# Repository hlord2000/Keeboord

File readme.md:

# Keeboord
## Created for the [Mechanical Keyboard Club at Georgia Tech](https://www.instagram.com/gt.keyboards)

This is a mechanical keyboard for Cherry switches.  It utilizes no diodes, instead registering button presses by using I2C I/O expanders.

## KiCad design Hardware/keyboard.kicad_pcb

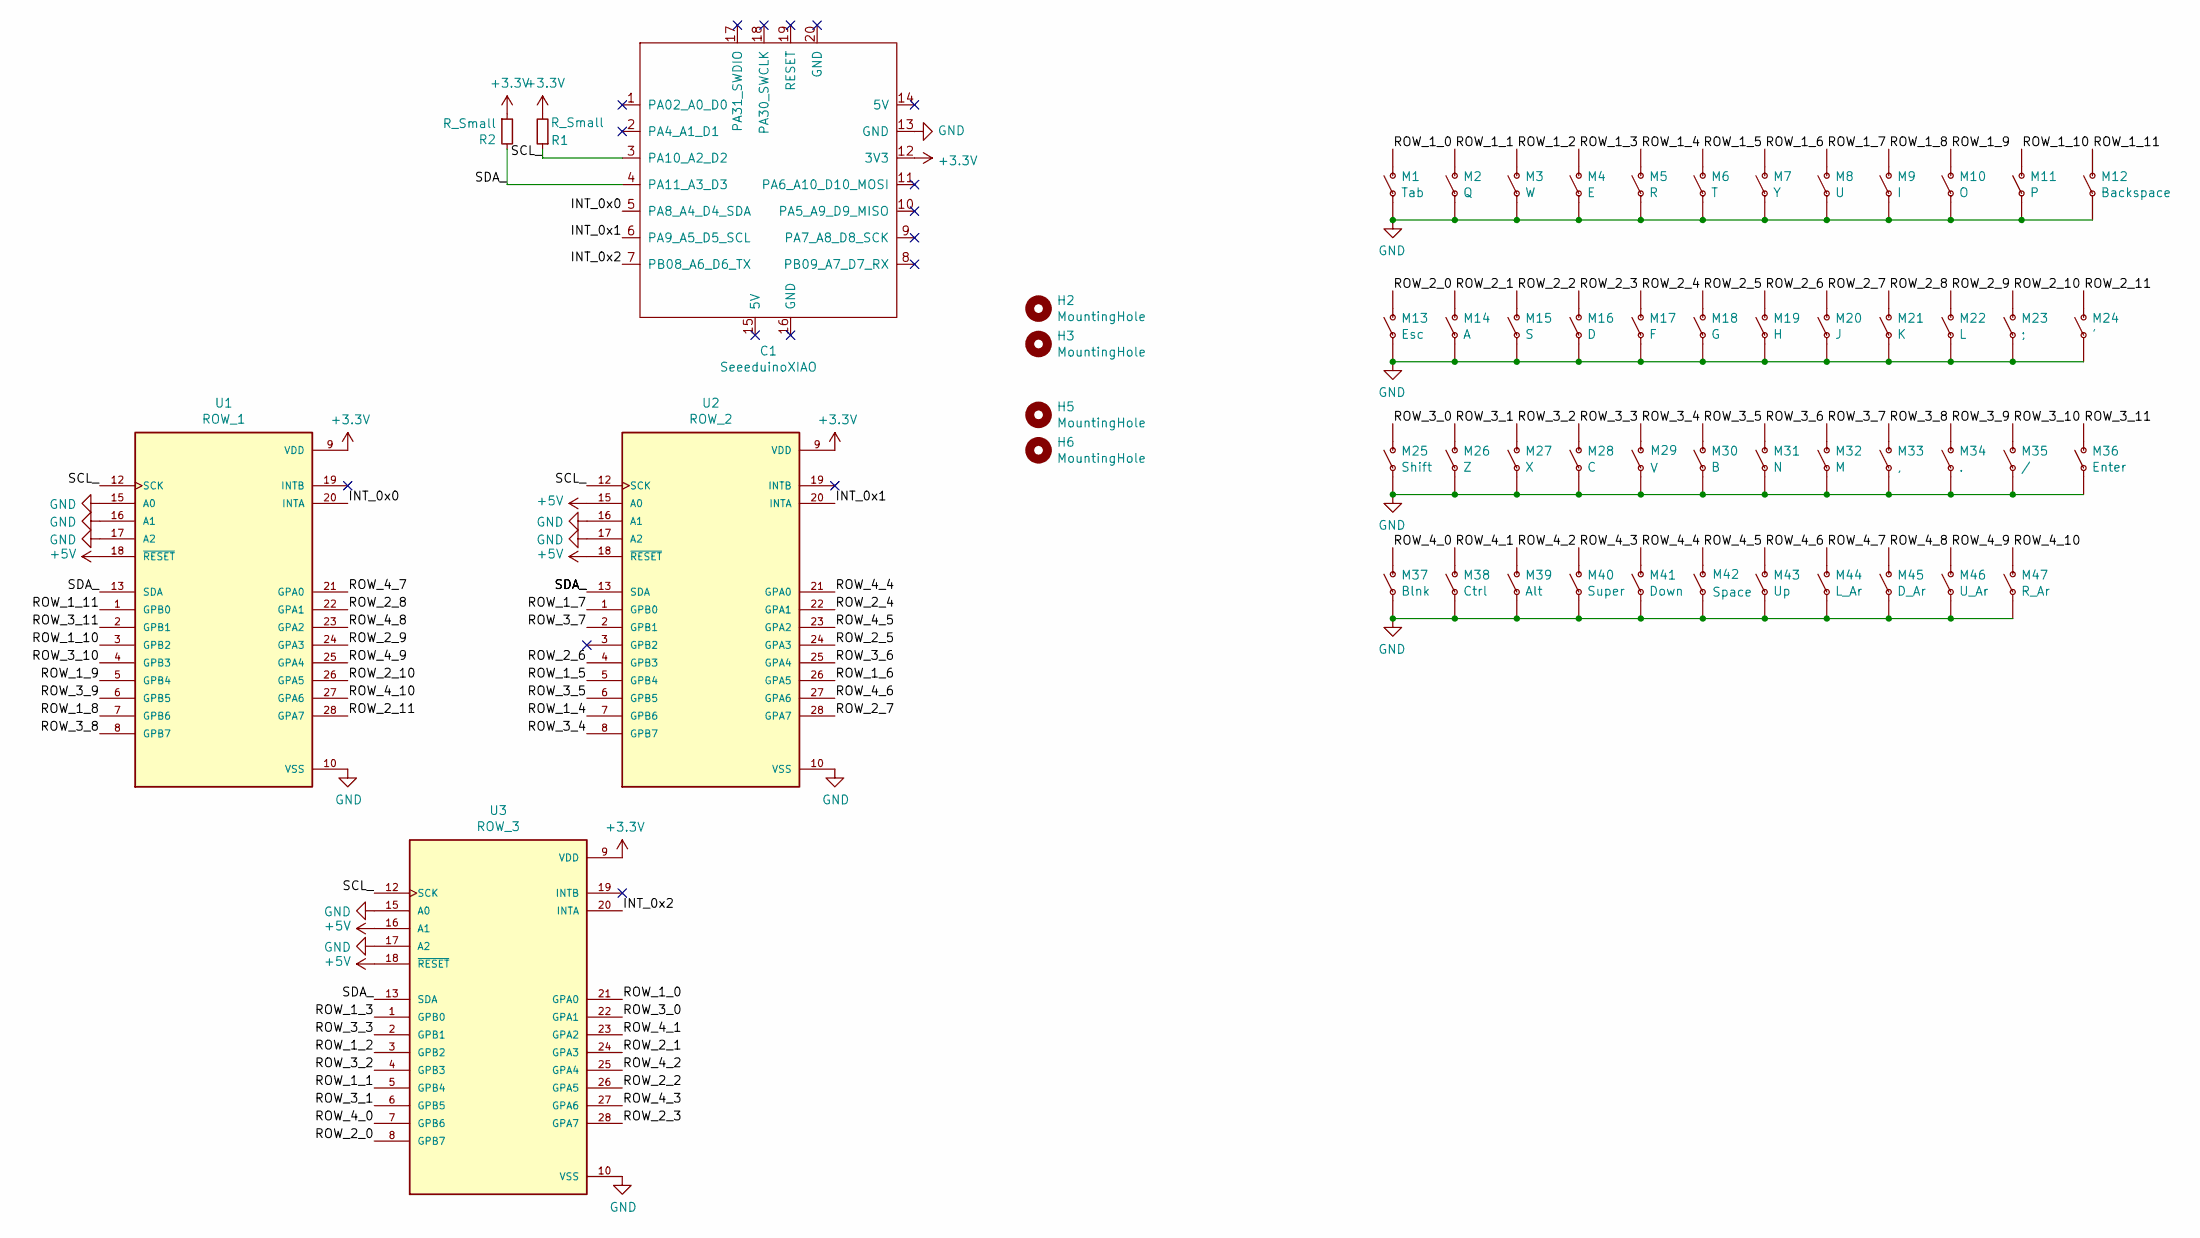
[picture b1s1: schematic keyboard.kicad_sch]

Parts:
C1: SeeeduinoXIAO; SeeeduinoXIAO-MOUDLE14P-2.54-21X17.8MM
H2, H3, H5, H6: MountingHole; MountingHole_3.2mm_M3_Pad
M1: Tab; SW_Cherry_MX_1.00u_PCB
M2: Q; SW_Cherry_MX_1.00u_PCB
M3: W; SW_Cherry_MX_1.00u_PCB
M4: E; SW_Cherry_MX_1.00u_PCB
M5: R; SW_Cherry_MX_1.00u_PCB
M6: T; SW_Cherry_MX_1.00u_PCB
M7: Y; SW_Cherry_MX_1.00u_PCB
M8: U; SW_Cherry_MX_1.00u_PCB
M9: I; SW_Cherry_MX_1.00u_PCB
M10: O; SW_Cherry_MX_1.00u_PCB
M11: P; SW_Cherry_MX_1.00u_PCB
M12: Backspace; SW_Cherry_MX_1.00u_PCB
M13: Esc; SW_Cherry_MX_1.00u_PCB
M14: A; SW_Cherry_MX_1.00u_PCB
M15: S; SW_Cherry_MX_1.00u_PCB
M16: D; SW_Cherry_MX_1.00u_PCB
M17: F; SW_Cherry_MX_1.00u_PCB
M18: G; SW_Cherry_MX_1.00u_PCB
M19: H; SW_Cherry_MX_1.00u_PCB
M20: J; SW_Cherry_MX_1.00u_PCB
M21: K; SW_Cherry_MX_1.00u_PCB
M22: L; SW_Cherry_MX_1.00u_PCB
M23: ;; SW_Cherry_MX_1.00u_PCB
M24: '; SW_Cherry_MX_1.00u_PCB
M25: Shift; SW_Cherry_MX_1.00u_PCB
M26: Z; SW_Cherry_MX_1.00u_PCB
M27: X; SW_Cherry_MX_1.00u_PCB
M28: C; SW_Cherry_MX_1.00u_PCB
M29: V; SW_Cherry_MX_1.00u_PCB
M30: B; SW_Cherry_MX_1.00u_PCB
M31: N; SW_Cherry_MX_1.00u_PCB
M32: M; SW_Cherry_MX_1.00u_PCB
M33: ,; SW_Cherry_MX_1.00u_PCB
M34: .; SW_Cherry_MX_1.00u_PCB
M35: /; SW_Cherry_MX_1.00u_PCB
M36: Enter; SW_Cherry_MX_1.00u_PCB
M37: Blnk; SW_Cherry_MX_1.00u_PCB
M38: Ctrl; SW_Cherry_MX_1.00u_PCB
M39: Alt; SW_Cherry_MX_1.00u_PCB
M40: Super; SW_Cherry_MX_1.00u_PCB
M41: Down; SW_Cherry_MX_1.00u_PCB
M42: Space; SW_Cherry_MX_2.00u_PCB
M43: Up; SW_Cherry_MX_1.00u_PCB
M44: L_Ar; SW_Cherry_MX_1.00u_PCB
M45: D_Ar; SW_Cherry_MX_1.00u_PCB
M46: U_Ar; SW_Cherry_MX_1.00u_PCB
M47: R_Ar; SW_Cherry_MX_1.00u_PCB
R1, R2: R_Small; R_Axial_DIN0204_L3.6mm_D1.6mm_P7.62mm_Horizontal
U1: ROW_1; DIP-28_W7.62mm
U2: ROW_2; DIP-28_W7.62mm
U3: ROW_3; DIP-28_W7.62mm

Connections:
+3V3: C1.12 (3V3), R1.2, R2.1, U1.9 (VDD), U1.18 (~RESET), U2.9 (VDD), U2.15 (A0), U2.18 (~RESET), U3.9 (VDD), U3.16 (A1), U3.18 (~RESET)
/INT_0x0: C1.5 (PA8_A4_D4_SDA), U1.20 (INTA)
/INT_0x1: C1.6 (PA9_A5_D5_SCL), U2.20 (INTA)
/INT_0x2: C1.7 (PB08_A6_D6_TX), U3.20 (INTA)
/ROW_1_0: M1.1 (O), U3.21 (GPA0)
/ROW_1_1: M2.1 (O), U3.5 (GPB4)
/ROW_1_2: M3.1 (O), U3.3 (GPB2)
/ROW_1_3: M4.1 (O), U3.1 (GPB0)
/ROW_1_4: M5.1 (O), U2.7 (GPB6)
/ROW_1_5: M6.1 (O), U2.5 (GPB4)
/ROW_1_6: M7.1 (O), U2.26 (GPA5)
/ROW_1_7: M8.1 (O), U2.1 (GPB0)
/ROW_1_8: M9.1 (O), U1.7 (GPB6)
/ROW_1_9: M10.1 (O), U1.5 (GPB4)
/ROW_1_10: M11.1 (O), U1.3 (GPB2)
/ROW_1_11: M12.1 (O), U1.1 (GPB0)
/ROW_2_0: M13.1 (O), U3.8 (GPB7)
/ROW_2_1: M14.1 (O), U3.24 (GPA3)
/ROW_2_2: M15.1 (O), U3.26 (GPA5)
/ROW_2_3: M16.1 (O), U3.28 (GPA7)
/ROW_2_4: M17.1 (O), U2.22 (GPA1)
/ROW_2_5: M18.1 (O), U2.24 (GPA3)
/ROW_2_6: M19.1 (O), U2.4 (GPB3)
/ROW_2_7: M20.1 (O), U2.28 (GPA7)
/ROW_2_8: M21.1 (O), U1.22 (GPA1)
/ROW_2_9: M22.1 (O), U1.24 (GPA3)
/ROW_2_10: M23.1 (O), U1.26 (GPA5)
/ROW_2_11: M24.1 (O), U1.28 (GPA7)
/ROW_3_0: M25.1 (O), U3.22 (GPA1)
/ROW_3_1: M26.1 (O), U3.6 (GPB5)
/ROW_3_2: M27.1 (O), U3.4 (GPB3)
/ROW_3_3: M28.1 (O), U3.2 (GPB1)
/ROW_3_4: M29.1 (O), U2.8 (GPB7)
/ROW_3_5: M30.1 (O), U2.6 (GPB5)
/ROW_3_6: M31.1 (O), U2.25 (GPA4)
/ROW_3_7: M32.1 (O), U2.2 (GPB1)
/ROW_3_8: M33.1 (O), U1.8 (GPB7)
/ROW_3_9: M34.1 (O), U1.6 (GPB5)
/ROW_3_10: M35.1 (O), U1.4 (GPB3)
/ROW_3_11: M36.1 (O), U1.2 (GPB1)
/ROW_4_0: M37.1 (O), U3.7 (GPB6)
/ROW_4_1: M38.1 (O), U3.23 (GPA2)
/ROW_4_2: M39.1 (O), U3.25 (GPA4)
/ROW_4_3: M40.1 (O), U3.27 (GPA6)
/ROW_4_4: M41.1 (O), U2.21 (GPA0)
/ROW_4_5: M42.1 (O), U2.23 (GPA2)
/ROW_4_6: M43.1 (O), U2.27 (GPA6)
/ROW_4_7: M44.1 (O), U1.21 (GPA0)
/ROW_4_8: M45.1 (O), U1.23 (GPA2)
/ROW_4_9: M46.1 (O), U1.25 (GPA4)
/ROW_4_10: M47.1 (O), U1.27 (GPA6)
/SCL_: C1.3 (PA10_A2_D2), R1.1, U1.12 (SCK), U2.12 (SCK), U3.12 (SCK)
/SDA_: C1.4 (PA11_A3_D3), R2.2, U1.13 (SDA), U2.13 (SDA), U3.13 (SDA)
GND: C1.13 (GND), M1.2, M2.2, M3.2, M4.2, M5.2, M6.2, M7.2, M8.2, M9.2, M10.2, M11.2, M12.2, M13.2, M14.2, M15.2, M16.2, M17.2, M18.2, M19.2, M20.2, M21.2, M22.2, M23.2, M24.2, M25.2, M26.2, M27.2, M28.2, M29.2, M30.2, M31.2, M32.2, M33.2, M34.2, M35.2, M36.2, M37.2, M38.2, M39.2, M40.2, M41.2, M42.2, M43.2, M44.2, M45.2, M46.2, M47.2, U1.10 (VSS), U1.15 (A0), U1.16 (A1), U1.17 (A2), U2.10 (VSS), U2.16 (A1), U2.17 (A2), U3.10 (VSS), U3.15 (A0), U3.17 (A2)

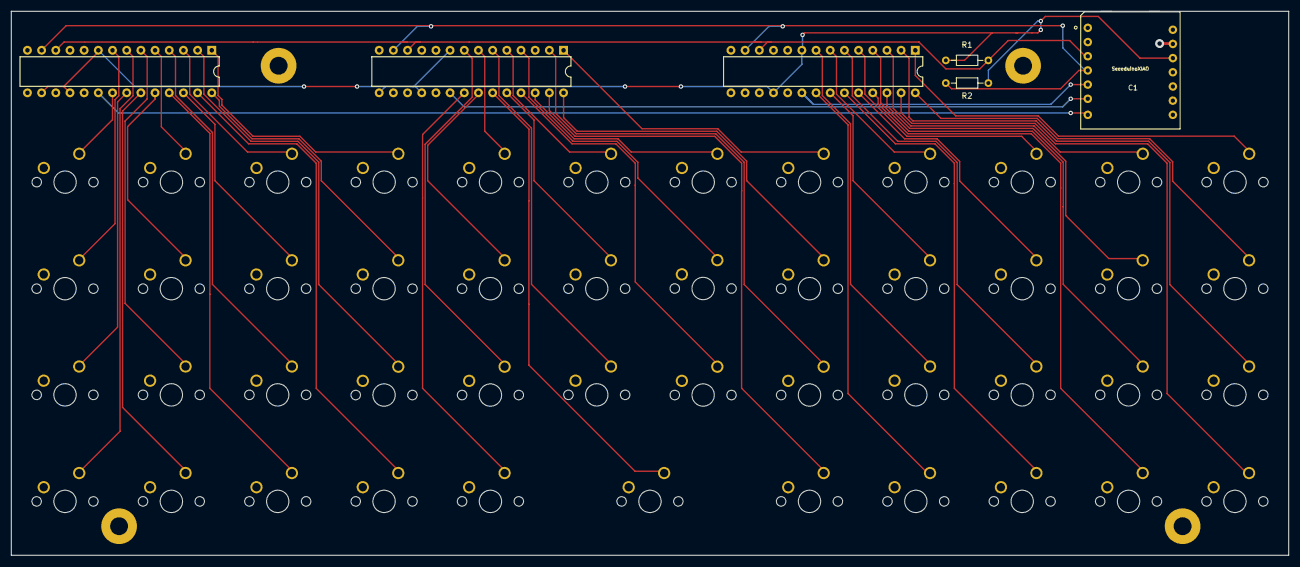
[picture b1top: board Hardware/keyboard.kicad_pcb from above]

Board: 2 copper layers, 228.8 x 97.4 mm, 57 parts (0 on the bottom side), 54 nets.

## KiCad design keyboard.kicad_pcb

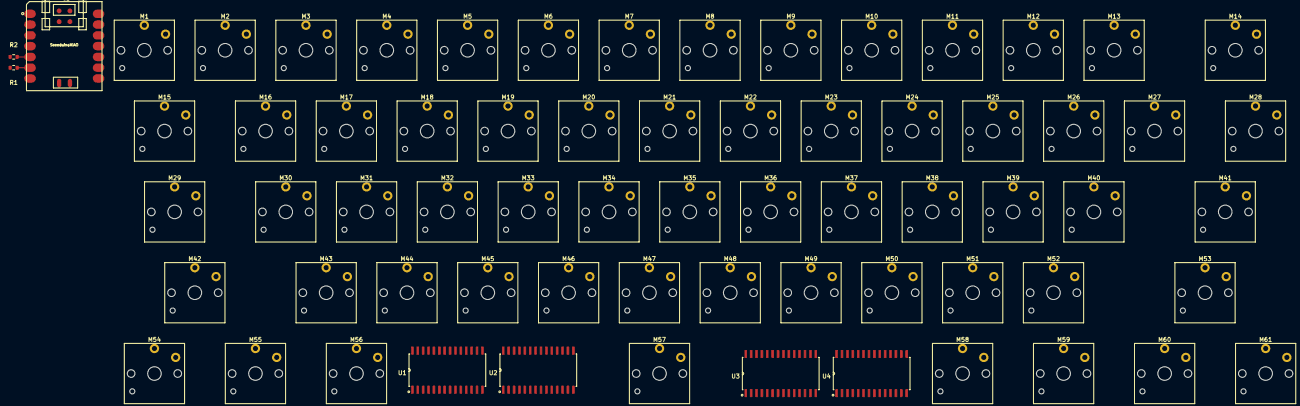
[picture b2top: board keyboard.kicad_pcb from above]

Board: 2 copper layers, 68 parts (0 on the bottom side), 69 nets.

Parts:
C1: SeeeduinoXIAO; Seeeduino XIAO-MOUDLE14P-2.54-21X17.8MM
M1: `; SW_Kailh_Choc_V1_1.00u
M2: 1; SW_Kailh_Choc_V1_1.00u
M3: 2; SW_Kailh_Choc_V1_1.00u
M4: 3; SW_Kailh_Choc_V1_1.00u
M5: 4; SW_Kailh_Choc_V1_1.00u
M6: 5; SW_Kailh_Choc_V1_1.00u
M7: 6; SW_Kailh_Choc_V1_1.00u
M8: 7; SW_Kailh_Choc_V1_1.00u
M9: 8; SW_Kailh_Choc_V1_1.00u
M10: 9; SW_Kailh_Choc_V1_1.00u
M11: 0; SW_Kailh_Choc_V1_1.00u
M12: -; SW_Kailh_Choc_V1_1.00u
M13: =; SW_Kailh_Choc_V1_1.00u
M14: Backspace; SW_Kailh_Choc_V1_2.00u
M15: Tab; SW_Kailh_Choc_V1_1.50u
M16: Q; SW_Kailh_Choc_V1_1.00u
M17: W; SW_Kailh_Choc_V1_1.00u
M18: E; SW_Kailh_Choc_V1_1.00u
M19: R; SW_Kailh_Choc_V1_1.00u
M20: T; SW_Kailh_Choc_V1_1.00u
M21: Y; SW_Kailh_Choc_V1_1.00u
M22: U; SW_Kailh_Choc_V1_1.00u
M23: I; SW_Kailh_Choc_V1_1.00u
M24: O; SW_Kailh_Choc_V1_1.00u
M25: P; SW_Kailh_Choc_V1_1.00u
M26: [; SW_Kailh_Choc_V1_1.00u
M27: ]; SW_Kailh_Choc_V1_1.00u
M28: \; SW_Kailh_Choc_V1_1.50u
M29: CapsLock; SW_Kailh_Choc_V1_1.75u
M30: A; SW_Kailh_Choc_V1_1.00u
M31: S; SW_Kailh_Choc_V1_1.00u
M32: D; SW_Kailh_Choc_V1_1.00u
M33: F; SW_Kailh_Choc_V1_1.00u
M34: G; SW_Kailh_Choc_V1_1.00u
M35: H; SW_Kailh_Choc_V1_1.00u
M36: J; SW_Kailh_Choc_V1_1.00u
M37: K; SW_Kailh_Choc_V1_1.00u
M38: L; SW_Kailh_Choc_V1_1.00u
M39: ;; SW_Kailh_Choc_V1_1.00u
M40: '; SW_Kailh_Choc_V1_1.00u
M41: Enter; SW_Kailh_Choc_V1_2.25u
M42: LeftShift; SW_Kailh_Choc_V1_2.25u
M43: Z; SW_Kailh_Choc_V1_1.00u
M44: X; SW_Kailh_Choc_V1_1.00u
M45: C; SW_Kailh_Choc_V1_1.00u
M46: V; SW_Kailh_Choc_V1_1.00u
M47: B; SW_Kailh_Choc_V1_1.00u
M48: N; SW_Kailh_Choc_V1_1.00u
M49: M; SW_Kailh_Choc_V1_1.00u
M50: ,; SW_Kailh_Choc_V1_1.00u
M51: .; SW_Kailh_Choc_V1_1.00u
M52: /; SW_Kailh_Choc_V1_1.00u
M53: RightShift; SW_Kailh_Choc_V1_2.75u
M54: LeftCtrl; SW_Kailh_Choc_V1_1.25u
M55: LeftSuper; SW_Kailh_Choc_V1_1.25u
M56: LeftAlt; SW_Kailh_Choc_V1_1.25u
M57: SpaceBar; SW_Kailh_Choc_V1_6.25u
M58: RightAlt; SW_Kailh_Choc_V1_1.25u
M59: RightSuper; SW_Kailh_Choc_V1_1.25u
M60: Menu; SW_Kailh_Choc_V1_1.25u
M61: RightCtrl; SW_Kailh_Choc_V1_1.25u
R1, R2: 10k; R_0603_1608Metric
U1: ROW_1_2; SOIC127P1030X265-28N
U2: ROW_3_4; SOIC127P1030X265-28N
U3: ROW_5_6; SOIC127P1030X265-28N
U4: ROW_7_8; SOIC127P1030X265-28N

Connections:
+5V: C1.14, R1.1, R2.2, U1.9, U2.9, U2.15, U3.9, U3.16, U4.9, U4.15, U4.16
/INT_0x0: C1.1, U1.19, U1.20
/INT_0x1: C1.2, U2.19, U2.20
/INT_0x2: C1.3, U3.19, U3.20
/INT_0x3: C1.4, U4.19, U4.20
/ROW_1_0: M1.1, U1.21
/ROW_1_1: M2.1, U1.22
/ROW_1_2: M3.1, U1.23
/ROW_1_3: M4.1, U1.24
/ROW_1_4: M5.1, U1.25
/ROW_1_5: M6.1, U1.26
/ROW_1_6: M7.1, U1.27
/ROW_1_7: M8.1, U1.28
/ROW_2_0: M9.1, U1.1
/ROW_2_1: M10.1, U1.2
/ROW_2_2: M11.1, U1.3
/ROW_2_3: M12.1, U1.4
/ROW_2_4: M13.1, U1.5
/ROW_2_5: M14.1, U1.6
/ROW_2_6: M15.1, U1.7
/ROW_2_7: M16.1, U1.8
/ROW_3_0: M17.1, U2.21
/ROW_3_1: M18.1, U2.22
/ROW_3_2: M19.1, U2.23
/ROW_3_3: M20.1, U2.24
/ROW_3_4: M21.1, U2.25
/ROW_3_5: M22.1, U2.26
/ROW_3_6: M23.1, U2.27
/ROW_3_7: M24.1, U2.28
/ROW_4_0: M25.1, U2.1
/ROW_4_1: M26.1, U2.2
/ROW_4_2: M27.1, U2.3
/ROW_4_3: M28.1, U2.4
/ROW_4_4: M29.1, U2.5
/ROW_4_5: M30.1, U2.6
/ROW_4_6: M31.1, U2.7
/ROW_4_7: M32.1, U2.8
/ROW_5_0: M33.1, U3.21
/ROW_5_1: M34.1, U3.22
/ROW_5_2: M35.1, U3.23
/ROW_5_3: M36.1, U3.24
/ROW_5_4: M37.1, U3.25
/ROW_5_5: M38.1, U3.26
/ROW_5_6: M39.1, U3.27
/ROW_5_7: M40.1, U3.28
/ROW_6_0: M41.1, U3.1
/ROW_6_1: M42.1, U3.2
/ROW_6_2: M43.1, U3.3
/ROW_6_3: M44.1, U3.4
/ROW_6_4: M45.1, U3.5
/ROW_6_5: M46.1, U3.6
/ROW_6_6: M47.1, U3.7
/ROW_6_7: M48.1, U3.8
/ROW_7_0: M49.1, U4.21
/ROW_7_1: M50.1, U4.22
/ROW_7_2: M51.1, U4.23
/ROW_7_3: M52.1, U4.24
/ROW_7_4: M53.1, U4.25
/ROW_7_5: M54.1, U4.26
/ROW_7_6: M55.1, U4.27
/ROW_7_7: M56.1, U4.28
/ROW_8_0: M57.1, U4.1
/ROW_8_1: M58.1, U4.2
/ROW_8_2: M59.1, U4.3
/ROW_8_3: M60.1, U4.4
/ROW_8_4: M61.1, U4.5
/SCL_: C1.6, R1.2, U1.12, U2.12, U3.12, U4.12
/SDA_: C1.5, R2.1, U1.13, U2.13, U3.13, U4.13
GND: C1.13, M1.2, M2.2, M3.2, M4.2, M5.2, M6.2, M7.2, M8.2, M9.2, M10.2, M11.2, M12.2, M13.2, M14.2, M15.2, M16.2, M17.2, M18.2, M19.2, M20.2, M21.2, M22.2, M23.2, M24.2, M25.2, M26.2, M27.2, M28.2, M29.2, M30.2, M31.2, M32.2, M33.2, M34.2, M35.2, M36.2, M37.2, M38.2, M39.2, M40.2, M41.2, M42.2, M43.2, M44.2, M45.2, M46.2, M47.2, M48.2, M49.2, M50.2, M51.2, M52.2, M53.2, M54.2, M55.2, M56.2, M57.2, M58.2, M59.2, M60.2, M61.2, U1.10, U1.15, U1.16, U1.17, U2.10, U2.16, U2.17, U3.10, U3.15, U3.17, U4.10, U4.17

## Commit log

2021-10-29 Initial hardware Rev. 1
2021-10-29 small revision
2021-10-29 Reworked layout, everything is aligned now.
2021-10-29 routing
2021-10-30 Prototype 1
2021-10-30 Cleaned up file structure.
2021-10-30 License.
2021-10-31 Rerouting
2021-11-02 South-facing switch change
2021-11-02 Change
2021-11-02 More rerouting.
2021-11-02 Yet more rerouting.
2021-11-03 Added MX switch compatibility
2021-11-06 Rerouting.
2021-11-07 Moved location of I/O
2021-11-07 updated output files.
2021-11-12 Conversion to all through-hole components.
2021-11-21 Added image.
2021-11-23 Swapped SDA and SCL pins.
2022-01-20 Firmware added.
2022-01-22 Final revision of hardware, software, art.
2022-01-22 Changed display image.
